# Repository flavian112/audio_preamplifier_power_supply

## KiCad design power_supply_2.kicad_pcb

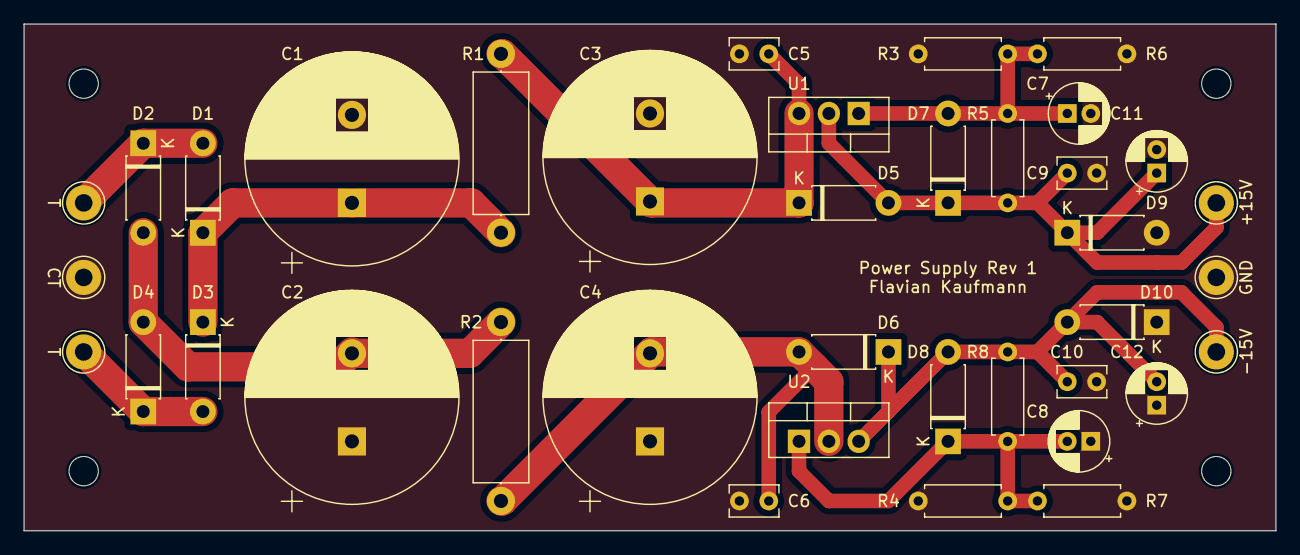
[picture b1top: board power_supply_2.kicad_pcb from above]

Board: 2 copper layers, 106.7 x 43.2 mm, 32 parts (0 on the bottom side), 11 nets.

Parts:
C1, C2, C3, C4: 2200u; CP_Radial_D18.0mm_P7.50mm
C5, C6, C9, C10: 100n; C_Rect_L4.0mm_W2.5mm_P2.50mm
C7, C8, C11, C12: 10u; CP_Radial_D5.0mm_P2.00mm
D1, D2, D3, D4, D5, D6, D7, D8, D9, D10: 1N4004; D_DO-41_SOD81_P7.62mm_Horizontal
R1, R2: 10R; R_Axial_DIN0414_L11.9mm_D4.5mm_P15.24mm_Horizontal
R3, R4, R6, R7: 2k2; R_Axial_DIN0207_L6.3mm_D2.5mm_P7.62mm_Horizontal
R5, R8: 100R; R_Axial_DIN0207_L6.3mm_D2.5mm_P7.62mm_Horizontal
U1: LM317; TO-220-3_Vertical
U2: LM337; TO-220-3_Vertical

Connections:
+15: C9.1, C11.1, D5.2 (A), D7.1 (K), D9.1 (K), R5.1, U1.2 (VO)
-15: C10.2, C12.2, D6.1 (K), D8.2 (A), D10.2 (A), R8.2, U2.3 (VO)
GND: C1.2, C2.1, C3.2, C4.1, C5.2, C6.1, C7.2, C8.1, C9.2, C10.1, C11.2, C12.1, D9.2 (A), D10.1 (K), R3.2, R4.1, R6.2, R7.1
unnamed: C1.1, D1.1 (K), D3.1 (K), R1.1
unnamed: C2.2, D2.2 (A), D4.2 (A), R2.1
unnamed: C3.1, C5.1, D5.1 (K), R1.2, U1.3 (VI)
unnamed: C4.2, C6.2, D6.2 (A), R2.2, U2.2 (VI)
unnamed: C7.1, D7.2 (A), R3.1, R5.2, R6.1, U1.1 (ADJ)
unnamed: C8.2, D8.1 (K), R4.2, R7.2, R8.1, U2.1 (ADJ)
T+: D1.2 (A), D2.1 (K)
T-: D3.2 (A), D4.1 (K)

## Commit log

2024-02-04 cosmetics
